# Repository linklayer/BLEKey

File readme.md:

BLEKey
======

by Mark Baseggio and Eric Evenchick

BLEKey is a tool designed to demonstrate the risks of using the Wiegand protocol. 

[Here's a video](https://www.youtube.com/watch?v=seKas8KFcSI) of us talking about the BLEKey at Blackhat USA 2015.

You can get BLEKey here: http://store.cantact.io/products/blekey-1?variant=18261748871 **ANY OTHER STORE/SITE IS UNOFFICIAL** 

Building
--------

1. Download the GNU ARM Embedded Toolchain for your OS (gcc-arm-none-eabi-4_9-2015q1 was used to build this version): https://launchpad.net/gcc-arm-embedded/+download
2. Clone the repo: `git clone https://github.com/linklayer/BLEKey.git`
3. Edit the `Makefile.posix` file in the `BLEKey/gcc/` directory and make sure the path to the downloaded ARM toolchain is correct.
4. Change to the `BLEKey/gcc` directory and run `make`

If you have a Segger hooked up to the board you can also run:

* `make erase` to erase the nrf 
* `make flash-sd` to flash the soft device
* `make flash` to flash the compiled hex 

Flashing
--------

### Firmware Over the Air (FOTA)
We've included a file in the `/firmware` folder called `super.hex`. This firmware has a bootloader included that allows the BLEKey to be flashed from a cell phone by shorting the first and last pins of the P2 port, and inserting a battery. The firmware update has been tested on the Android platform using the Nordic Master Control Panel tool.

[We've created a video to demonstrate the process.](/firmware/fw_update.mp4)

### MacOS or Linux

To flash the softdevice and BLEKey firmware from the CLI you can use JLinkExe which is provided in the [Segger Software](https://www.segger.com/jlink-software.html)

The BLEKey requires a softdevice (for BLE) and the blekey firmware. These can be flashed using the commands below:

```
$ /usr/bin/JLinkExe -device nrf51822_xxaa -if swd -speed 4000

J-Link>loadbin s110_nrf51822_7.0.0_softdevice.bin 0
J-Link>loadbin blekey_s110_xxaa.hex 0x16000
J-Link>r
J-Link>g
```

Erasing:
```
J-Link>w4 4001e504 2
J-Link>w4 4001e50c 1
```

If you prefer a GUI you can always use [rknrfgo](http://sourceforge.net/projects/rknrfgo/)

The cheatsheet above is [ripped from Nordic's blog](https://devzone.nordicsemi.com/blogs/22/getting-started-with-nrf51-development-on-mac-os-x/)

### Windows

Use tools from Nordic.

Using BLEKey
------------

### BLE Characteristics
| Service  | Characteristic | Function
|----------|----------------|---------------
| 0xABCD   | 0xAAAA	 	    | Read Last Cards
| 0xABCD   | 0xBBBB			| Replay Card
| 0xABCD   | 0xCCCC			| Send Data (Data)
| 0xABCD   | 0xDDDD			| Send Data (Length)

### Client

There is a BLEKey client in the client/ directory of the git repo. See readme.md and requirements.txt for more information on its use.

### Phones/Tablets

A client is planned. Until then download any BLE utility that can read/write BLE characteristics. See below for more information on specific characteristics.

### CLI (Linux)

Find your Bluetooth device with `hcitool dev` scan for BLEKey with `hcitool -i <dev> lescan`

Start an interactive connection to BLEKey

Last three Wiegand cards are stored in the `0x000b` handle. Currently to cause BLEKey to send out the last read card on the Wiegand lines write to `0x000d`

```
[blark@archvm blekey]$ sudo gatttool -t random -b D4:34:E8:CA:6F:6A -I
[D4:34:E8:CA:6F:6A][LE]> connect
Attempting to connect to D4:34:E8:CA:6F:6A
Connection successful
[D4:34:E8:CA:6F:6A][LE]> characteristics
handle: 0x0002, char properties: 0x0a, char value handle: 0x0003, uuid: 00002a00-0000-1000-8000-00805f9b34fb
handle: 0x0004, char properties: 0x02, char value handle: 0x0005, uuid: 00002a01-0000-1000-8000-00805f9b34fb
handle: 0x0006, char properties: 0x02, char value handle: 0x0007, uuid: 00002a04-0000-1000-8000-00805f9b34fb
handle: 0x000a, char properties: 0x02, char value handle: 0x000b, uuid: 0000aaaa-0000-1000-8000-00805f9b34fb
handle: 0x000c, char properties: 0x08, char value handle: 0x000d, uuid: 0000bbbb-0000-1000-8000-00805f9b34fb
handle: 0x000e, char properties: 0x08, char value handle: 0x000f, uuid: 0000cccc-0000-1000-8000-00805f9b34fb
handle: 0x0010, char properties: 0x0a, char value handle: 0x0011, uuid: 0000dddd-0000-1000-8000-00805f9b34fb
handle: 0x0013, char properties: 0x12, char value handle: 0x0014, uuid: 00002a19-0000-1000-8000-00805f9b34fb
handle: 0x0017, char properties: 0x02, char value handle: 0x0018, uuid: 00002a29-0000-1000-8000-00805f9b34fb
[D4:34:E8:CA:6F:6A][LE]> char-write-req d 01
Characteristic value was written successfully
[D4:34:E8:CA:6F:6A][LE]> char-read-hnd b
Characteristic value/descriptor: 22 bd 58 60 7c 26 00 24 47 60 85 08 37 00 24 47 60 85 08 37 00 00 
[D4:34:E8:CA:6F:6A][LE]>
```

You can also just use gatttool from the command line to yell BLEKey to send Wiegand data (replace with the address of your device):
```
sudo gatttool -t random -b D4:34:E8:CA:6F:6A --char-write-req -a 0x000d -n 01
```

### Notes:

* Bluetooth Explorer is in the [Hardware IO Tools from Apple](http://adcdownload.apple.com/Developer_Tools/Hardware_IO_Tools_for_Xcode_6.3/HardwareIOTools_Xcode_6.3.dmg) it's probably the best BLE utility for Mac.

Pinouts
-------

### Harware rev. 0 code name Acamas

| Pin	| Function 		|
| ------|---------------|
| 0     | Data 0 in 	|
| 1		| Data 1 in		|
| 2     | Data 0 ctl	|
| 3		| Data 1 ctl	|
| 9		| Serial		|
| 11	| Serial		|
| 26	| Xtal 1		|
| 27	| Xtal 2		|
| 28	| GPIO			|
| 29	| GPIO			|
| 35	| DIO			|
| 36	| CLK			|

### Hardware rev. 1 Agapenor

Pinouts are identical to Acamas unless otherwise noted.

| Pin	| Function 		|
| ------|---------------|
| 0     | Data 0 in 	|
| 7		| Data 1 in		|
| 8		| GPIO			|
| 20	| LED0			|

#### P1 - Programming port (square solder mask pin 0)

| Pin	| Function 		|
| ------|---------------|
| 0     | Vcc		 	|
| 1		| DIO			|
| 2		| CLK			|
| 3     | Gnd			|

#### P2 - Serial/GPIO port (square solder mask pin 0)

| Pin	| Function 		|
| ------|---------------|
| 0     | GPIO (Tx)	 	|
| 1		| DATA0			|
| 2		| DATA1			|
| 3     | Gnd			|

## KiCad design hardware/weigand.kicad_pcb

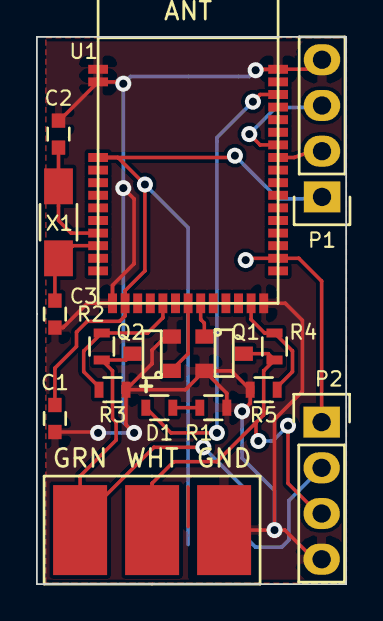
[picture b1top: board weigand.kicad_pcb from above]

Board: 2 copper layers, 17.2 x 30.4 mm, 17 parts (1 on the bottom side), 15 nets.

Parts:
BATT1: CR2032; BU1632SM-JJ-GTR
C1: 100nF; C_0603
C2, C3: 12pF; C_0603
D1: LED; R_0603
K1: WIEGAND; IDC3POS
P1, P2: CONN_01X04; Pin_Header_Straight_1x04
Q1, Q2: FET_N; SOT-23-FET
R1, R2, R3, R4, R5: R; R_0603
U1: MDBT40
X1: 32.768kHz; C_1206_HandSoldering

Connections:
+BATT: BATT1.1, C1.2, P1.1, U1.3, U1.14
/D0_CTL: Q2.G, U1.19
/D0_SRC: R2.2, R3.1, U1.17
/D1_CTL: Q1.G, U1.20
/D1_SRC: R4.2, R5.1, U1.24
/DATA_0: K1.1, P2.2, Q2.D, R2.1
/DATA_1: K1.2, P2.3, Q1.D, R4.1
/LED_0: D1.1, U1.40
/SW_CLK: P1.3, U1.36
/SW_DIO: P1.2, U1.35
/TX_TTL: P2.1, U1.27
/XL1: C2.1, U1.9, X1.1
/XL2: C3.1, U1.10, X1.2
GND: BATT1.2, C1.1, C2.2, C3.2, K1.3, P1.4, P2.4, Q1.S, Q2.S, R1.2, R3.2, R5.2, U1.1, U1.2, U1.13, U1.25, U1.42
unnamed: D1.2, R1.1

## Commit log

2015-03-04 ignore build artifacts
2015-03-04 make Makefile into a simlink
2015-05-27 enabled debug info
2015-05-27 all BLE characteristics working for wiegand service
2015-05-28 added code for wiegand, not integrated yet
2015-05-28 removed old hex file
2015-05-28 removed LED inits
2015-05-28 readded LED inits
2015-05-28 changed to RC osc
2015-05-28 dos2unix'd
2015-05-28 added retarget for UART debug
2015-05-28 added debug message
2015-05-28 changed around retarget init
2015-05-28 remapped LEDs
2015-05-29 switched wiegand to GPIOTE
2015-05-29 GPIOTE fixes
2015-05-29 added some comments
2015-05-29 added wiegand debug printing
2015-05-29 implemented wiegand task
2015-05-29 changed wiegand pins
2015-05-29 removed redundant pin inits
2015-05-29 disabled sleep
2015-05-29 removed GPIOTE library, switched to IRQ
2015-05-30 fixing wiegand stuff
2015-05-30 ble_app_hrs_uart_hci.Makefile deleted online with Bitbucket
2015-05-30 ble_app_hrs_uart.Makefile deleted online with Bitbucket
2015-05-30 ble_app_hrs_spi.Makefile deleted online with Bitbucket
2015-05-30 fixed makefile naming
2015-05-30 added nordic sdk and s110 softdevice to repo
2015-05-30 added Makefile.posix symbolic link
2015-05-30 makefile fixes and serial unfuck
2015-05-30 more makefile fixes
2015-05-30 fixed pins for serial again.. duh
2015-05-30 dos2unix main.c, enabled sleep
2015-05-30 wiegand print . instead of tick
2015-05-30 changed back to tick
2015-05-30 cleaned up old code
2015-05-30 removed sensor sim stuff
2015-05-31 added readme
2015-05-31 more readme stuff
2015-05-31 added docs dir with mdbt40 pinout jpg
2015-05-31 readme changes
2015-05-31 readme changes again
2015-05-31 fixed camelCase in wiegand.c
2015-05-31 dos2unix c files
2015-05-31 added serial debug printing to wiegand.c
2015-05-31 oops fixed typo
2015-05-31 interrupts actually working, timer fucked
2015-06-04 added wiegand to ble stuff
2015-06-05 main.c commented out garbage you left there, and wiegan.c fixes
2015-06-06 it works! ble advertising changed to 3sec interval, deep sleep disabled
2015-06-07 added uint64_t that stores complete card value and pad
2015-06-07 adding cards to struct for BLE transmision
2015-06-07 fixing data types and stuff
2015-06-07 cleaned up a bit and added comments
2015-06-08 removed data_bits array
2015-06-10 added send_wiegand boolean and start of weigand sending code
2015-06-10 added comments
2015-06-10 added send_wiegand function
2015-06-11 call send_wiegand on write
2015-06-12 added wiegand pwning! tx works!
2015-06-12 converted tabs to spaces
2015-06-12 added flash/erase to makefile
2015-06-12 added blog post link
2015-06-12 make flash improvements
2015-06-12 added pad_card routine, cleaned up some messy stuff
2015-06-12 added linux ble commands
2015-06-12 more linux infos
2015-06-30 serial improvements
2015-07-01 add_card didn't zero out memory before copying shorter cards, fixed memcpy hackery uglyness
2015-07-01 added linux python client
2015-07-01 fixed readme
2015-07-08 intergace stuff
2015-07-08 derp
2015-07-08 pin assignments
2015-07-08 commented stuff
2015-07-09 added hardware files
2015-07-09 readme improvements
2015-07-10 fixed shit that I broke
2015-07-10 made battery service work
2015-07-11 added battery read function
2015-07-11 added ability to use custom bluetooth device
2015-07-11 added passkey code
2015-07-15 added malloc for wiegand_ctx -- storing cards incrementally now
2015-07-15 compile size improvements
2015-07-18 bunch of shit
2015-07-18 flash-sd added
2015-07-19 fixed long reads
2015-07-19 ignore jlink scripts
2015-07-28 ble long writes, python client fixed
2015-07-29 added ctl card stuff, added firmware dir and superhex file
2015-07-29 added flashing instructions and video
2015-07-29 added link to video
2015-07-29 get value for card_id
2015-07-29 need to read a buffer...
2015-07-29 moved variables
2015-07-29 DoS features and control cards. No more BLEPenis. De-penised the Firmware
2015-08-02 more readme improvements
2015-08-03 fixed some spacing stuff
2015-08-05 fixed all the things that were super broke before our talk, beer time!
2015-08-08 final code from BH USA demos
2015-08-08 removed garbage file...
2016-02-22 updated hardwware
2016-03-04 Added blackhat video
2016-07-28 initial commit of bootloader
2016-07-28 mergehex from nrf tools
2016-08-07 Added store info
2017-03-15 added characteristic info to readme
2017-03-15 readme formatting fixes
